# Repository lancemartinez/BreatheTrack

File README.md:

# BreatheTrack

## Prototype 1

## Assembled Prototype 1 

## Prototype 2

## Bill of Materials (BOM)

| Component                           | Quantity | Price Estimate | Link |
|-------------------------------------|----------|----------------|------|
| PCB                                 | 1        | $60            | [JLCPCB](https://jlcpcb.com) |
| 6V 1W Solar Cell                     | 5        | $16            | [Amazon](https://www.amazon.com/gp/product/B0BML3PR4Z/ref=ox_sc_act_title_1?smid=A2MJCDED57HY1D&th=1) |
| MakerFocus ESP32 LoRa V3 Dev Board (with 2x SX1262 + 2x Battery) | 1 | $53 | [Amazon](https://www.amazon.com/gp/product/B0DMSGL2DC/ref=ox_sc_act_title_1?smid=A1N6DLY3NQK2VM&th=1) |
| Solar Panel Power Manager           | 1        | $14            | [Amazon](https://www.amazon.com/gp/product/B07MML4YJV/ref=ox_sc_act_title_4?smid=A2EH5PO307BR7O&psc=1) |
| Breadboard, Resistors, LEDs Kit     | 1        | $10            | [Amazon](https://www.amazon.com/dp/B01ERP6WL4) |
| Soldering Iron                      | 1        | $9             | [Amazon](https://www.amazon.com/Soldering-Welding-Portable-Electric-Repairing/dp/B098JD8HD3) |
| Total                        | 10          | $162             | N/A |

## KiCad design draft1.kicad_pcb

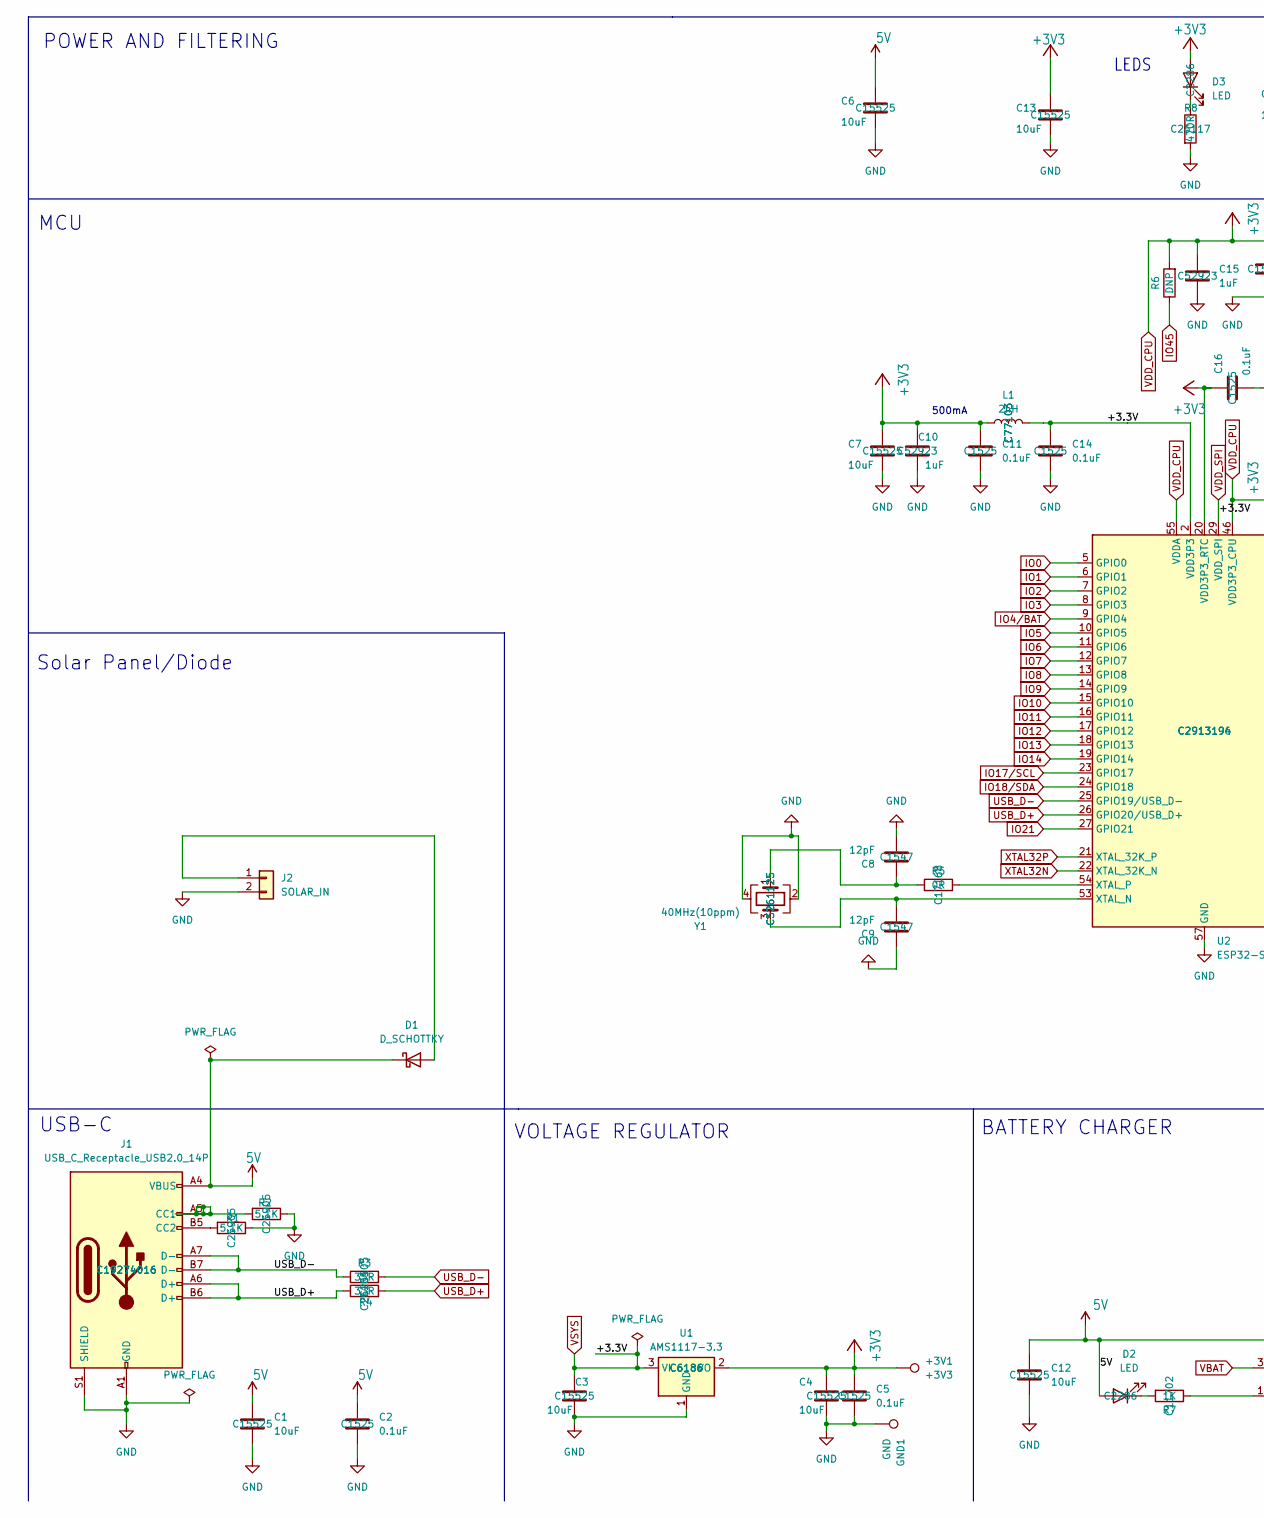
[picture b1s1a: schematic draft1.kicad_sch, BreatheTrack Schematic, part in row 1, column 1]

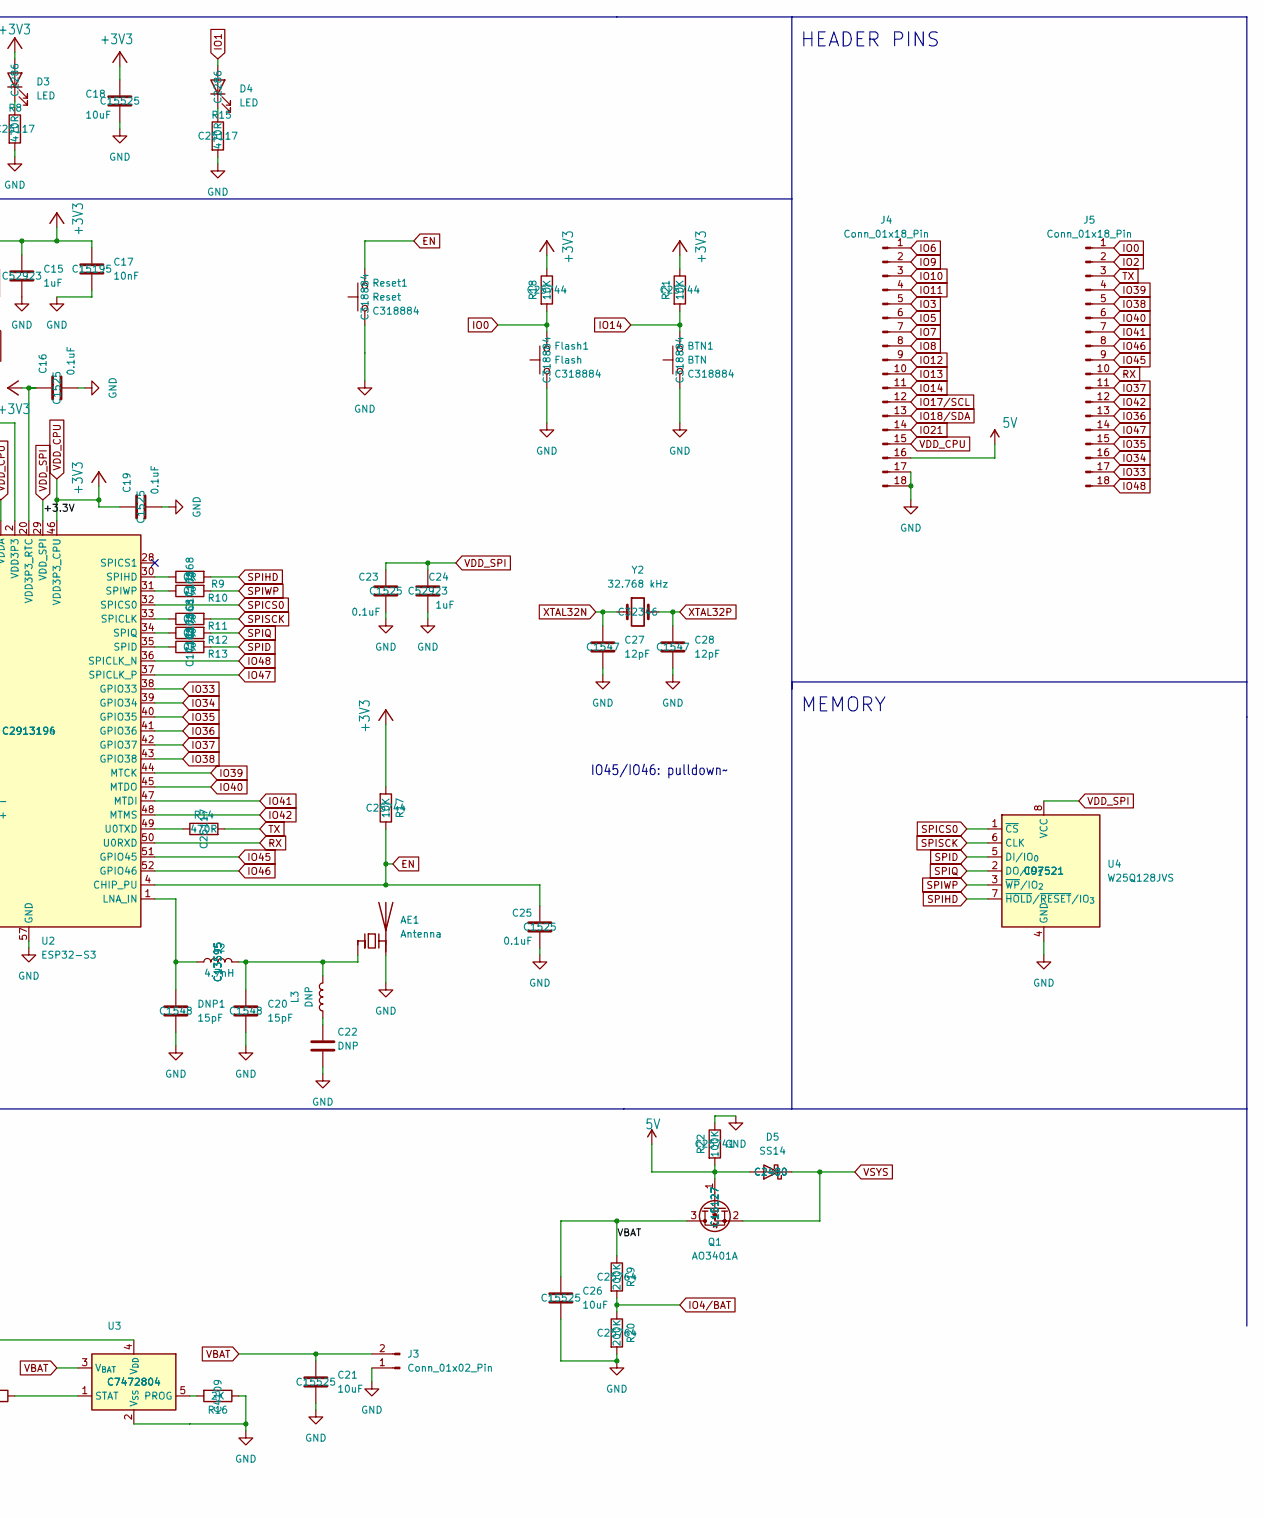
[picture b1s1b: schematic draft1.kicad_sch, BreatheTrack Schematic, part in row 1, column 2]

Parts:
+3V1: +3V3; TestPoint_Pad_D1.0mm
AE1: Antenna; Texas_SWRA117D_2.4GHz_Left
BTN1: BTN; SW_Push_1P1T_XKB_TS-1187A; MNF PART NUMBER C318884; LCSC C318884
C1, C3, C4, C6, C7, C12, C13, C18, C21, C26: 10uF; C_0402_1005Metric; MNF PART NUMBER C15525; LCSC C15525
C2, C5, C11, C14, C16, C19, C23, C25: 0.1uF; C_0402_1005Metric; MNF PART NUMBER C1525; LCSC C1525
C8, C9, C27, C28: 12pF; C_0402_1005Metric; MNF PART NUMBER C1547; LCSC C1547
C10, C15, C24: 1uF; C_0402_1005Metric; MNF PART NUMBER C52923; LCSC C52923
C17: 10nF; C_0402_1005Metric; MNF PART NUMBER C15195; LCSC C15195
C20: 15pF; C_0402_1005Metric; MNF PART NUMBER C1548; LCSC C1548
C22: DNP; C_0402_1005Metric
D1: D_SCHOTTKY; D_SMA
D2, D3, D4: LED; LED_0603_1608Metric; MNF PART NUMBER C2286; LCSC C2286
D5: SS14; D_SMA; MNF PART NUMBER C2480; LCSC C2480
DNP1: 15pF; C_0402_1005Metric; MNF PART NUMBER C1548; LCSC C1548
Flash1: Flash; SW_Push_1P1T_XKB_TS-1187A; MNF PART NUMBER C318884; LCSC C318884
GND1: GND; TestPoint_Pad_D1.0mm
J1: USB_C_Receptacle_USB2.0_14P; USB_C_Receptacle_HCTL_HC-TYPE-C-16P-01A; MNF PART NUMBER C19274016; LCSC C19274016
J2: SOLAR_IN; JST_PH_S2B-PH-SM4-TB_1x02-1MP_P2.00mm_Horizontal
J3: Conn_01x02_Pin; PinSocket_1x02_P2.54mm_Vertical
J4, J5: Conn_01x18_Pin; PinHeader_1x18_P2.54mm_Vertical
L1: 2nH; L_0402_1005Metric; MNF PART NUMBER C77103; LCSC C77103
L2: 4.7nH; L_0402_1005Metric; MNF PART NUMBER C13595; LCSC C13595
L3: DNP; L_0402_1005Metric
Q1: AO3401A; SOT-23; MNF PART NUMBER C15127; LCSC C15127
R1, R2: 5.1K; R_0402_1005Metric; MNF PART NUMBER C25905; LCSC C25905
R3, R4: 33R; R_0402_1005Metric; MNF PART NUMBER C25105; LCSC C25105
R5, R9, R10, R11, R12, R13: 0R; R_0402_1005Metric; MNF PART NUMBER C17168; LCSC C17168
R6: DNP; R_0402_1005Metric
R7: 1K; R_0402_1005Metric; MNF PART NUMBER C11702; LCSC C11702
R8, R14, R15: 470R; R_0402_1005Metric; MNF PART NUMBER C25117; LCSC C25117
R16: 2K; R_0402_1005Metric; MNF PART NUMBER C4109; LCSC C4109
R17, R18, R21: 10K; R_0402_1005Metric; MNF PART NUMBER C25744; LCSC C25744
R19, R20: 200K; R_0402_1005Metric; MNF PART NUMBER C25764; LCSC C25764
R22: 100K; R_0402_1005Metric; MNF PART NUMBER C25741; LCSC C25741
Reset1: Reset; SW_Push_1P1T_XKB_TS-1187A; MNF PART NUMBER C318884; LCSC C318884
U1: AMS1117-3.3; SOT-223-3_TabPin2; MNF PART NUMBER C6186; LCSC C6186
U2: ESP32-S3; QFN-56-1EP_7x7mm_P0.4mm_EP4x4mm; MNF PART NUMBER C2913196; LCSC C2913194
U3: MCP73831-2-OT; SOT-23-5; MNF PART NUMBER C7472804; LCSC C7472804
U4: W25Q128JVS; SOIC-8_5.3x5.3mm_P1.27mm; MNF PART NUMBER C97521; LCSC C97521
Y1: 40MHz(10ppm); Crystal_SMD_2520-4Pin_2.5x2.0mm; MNF PART NUMBER C5261125; LCSC C5261125
Y2: 32.768 kHz; Crystal_SMD_3215-2Pin_3.2x1.5mm; MNF PART NUMBER C32346; LCSC C32346

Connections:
5V: C1.1, C2.1, C6.1, C12.1, D1.1 (K), D2.2 (A), D5.2 (A), J1.A4 (VBUS), J1.A9 (VBUS), J1.B4 (VBUS), J1.B9 (VBUS), J4.16, Q1.1 (G), R22.2, U3.4 (V_{DD})
EN: C25.1, R17.1, Reset1.2, U2.4 (CHIP_PU)
GND: AE1.2 (PCB_Trace), BTN1.1, C1.2, C2.2, C3.2, C4.2, C5.2, C6.2, C7.2, C8.2, C9.1, C10.2, C11.2, C12.2, C13.2, C14.2, C15.2, C16.2, C17.2, C18.2, C19.2, C20.2, C21.2, C22.2, C23.2, C24.2, C25.2, C26.2, C27.2, C28.2, DNP1.2, Flash1.1, GND1.1, J1.A1 (GND), J1.A12 (GND), J1.B1 (GND), J1.B12 (GND), J1.S1 (SHIELD), J2.2, J3.1, J4.17, J4.18, R1.1, R2.1, R8.2, R15.2, R16.1, R20.2, R22.1, Reset1.1, U1.1 (GND), U2.57 (GND), U3.2 (V_{SS}), U4.4 (GND), Y1.2, Y1.4
IO0: Flash1.2, J5.1, R18.2, U2.5 (GPIO0)
IO1: D4.2 (A), U2.6 (GPIO1)
IO2: J5.2, U2.7 (GPIO2)
IO3: J4.5, U2.8 (GPIO3)
IO4/BAT: R19.2, R20.1, U2.9 (GPIO4)
IO5: J4.6, U2.10 (GPIO5)
IO6: J4.1, U2.11 (GPIO6)
IO7: J4.7, U2.12 (GPIO7)
IO8: J4.8, U2.13 (GPIO8)
IO9: J4.2, U2.14 (GPIO9)
IO10: J4.3, U2.15 (GPIO10)
IO11: J4.4, U2.16 (GPIO11)
IO12: J4.9, U2.17 (GPIO12)
IO13: J4.10, U2.18 (GPIO13)
IO14: BTN1.2, J4.11, R21.2, U2.19 (GPIO14)
IO17/SCL: J4.12, U2.23 (GPIO17)
IO18/SDA: J4.13, U2.24 (GPIO18)
IO21: J4.14, U2.27 (GPIO21)
IO33: J5.17, U2.38 (GPIO33)
IO34: J5.16, U2.39 (GPIO34)
IO35: J5.15, U2.40 (GPIO35)
IO36: J5.13, U2.41 (GPIO36)
IO37: J5.11, U2.42 (GPIO37)
IO38: J5.5, U2.43 (GPIO38)
IO39: J5.4, U2.44 (MTCK)
IO40: J5.6, U2.45 (MTDO)
IO41: J5.7, U2.47 (MTDI)
IO42: J5.12, U2.48 (MTMS)
IO45: J5.9, R6.1, U2.51 (GPIO45)
IO46: J5.8, U2.52 (GPIO46)
IO47: J5.14, U2.37 (SPICLK_P)
IO48: J5.18, U2.36 (SPICLK_N)
unnamed: AE1.1 (FEED), C20.1, L2.2, L3.2
unnamed: C8.1, R5.1, Y1.1
unnamed: C22.1, L3.1
unnamed: D1.2 (A), J2.1
unnamed: D2.1 (K), R7.2
unnamed: D3.1 (K), R8.1
unnamed: D4.1 (K), R15.1
unnamed: J1.A5 (CC1), R2.2
unnamed: J1.B5 (CC2), R1.2
unnamed: DNP1.1, L2.1, U2.1 (LNA_IN)
unnamed: R11.1, U2.33 (SPICLK)
unnamed: R13.1, U2.35 (SPID)
unnamed: R9.1, U2.30 (SPIHD)
unnamed: R12.1, U2.34 (SPIQ)
unnamed: R10.1, U2.31 (SPIWP)
unnamed: R14.1, U2.49 (U0TXD)
unnamed: C9.2, U2.53 (XTAL_N), Y1.3
unnamed: R5.2, U2.54 (XTAL_P)
unnamed: R16.2, U3.5 (PROG)
unnamed: R7.1, U3.1 (STAT)
RX: J5.10, U2.50 (U0RXD)
SPICS0: U2.32 (SPICS0), U4.1 (~CS)
SPID: R13.2, U4.5 (DI/IO_{0})
SPIHD: R9.2, U4.7 (~HOLD/~RESET/IO_{3})
SPIQ: R12.2, U4.2 (DO/IO_{1})
SPISCK: R11.2, U4.6 (CLK)
SPIWP: R10.2, U4.3 (~WP/IO_{2})
TX: J5.3, R14.2
USB_D+: J1.A6 (D+), J1.B6 (D+), R4.1, R4.2, U2.26 (GPIO20/USB_D+)
USB_D-: J1.A7 (D-), J1.B7 (D-), R3.1, R3.2, U2.25 (GPIO19/USB_D-)
VBAT: C21.1, C26.1, J3.2, Q1.3 (D), R19.1, U3.3 (V_{BAT})
VDD_CPU: +3V1.1, C4.1, C5.1, C7.1, C10.1, C11.1, C13.1, C15.1, C16.1, C17.1, C18.1, C19.1, D3.2 (A), J4.15, L1.1, R6.2, R17.2, R18.1, R21.1, U1.2 (VO), U2.20 (VDD3P3_RTC), U2.46 (VDD3P3_CPU), U2.55 (VDDA), U2.56 (VDDA)
VDD_SPI: C3.1, C14.1, C23.1, C24.1, D5.1 (K), L1.2, Q1.2 (S), U1.3 (VI), U2.2 (VDD3P3), U2.3 (VDD3P3), U2.29 (VDD_SPI), U4.8 (VCC)
XTAL32N: C27.1, U2.22 (XTAL_32K_N), Y2.1
XTAL32P: C28.1, U2.21 (XTAL_32K_P), Y2.2

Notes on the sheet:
Solar Panel/Diode
500mA
MCU
USB-C
BATTERY CHARGER
MEMORY
VOLTAGE REGULATOR
IO45/IO46: pulldown~~{}
POWER AND FILTERING
HEADER PINS
LEDS

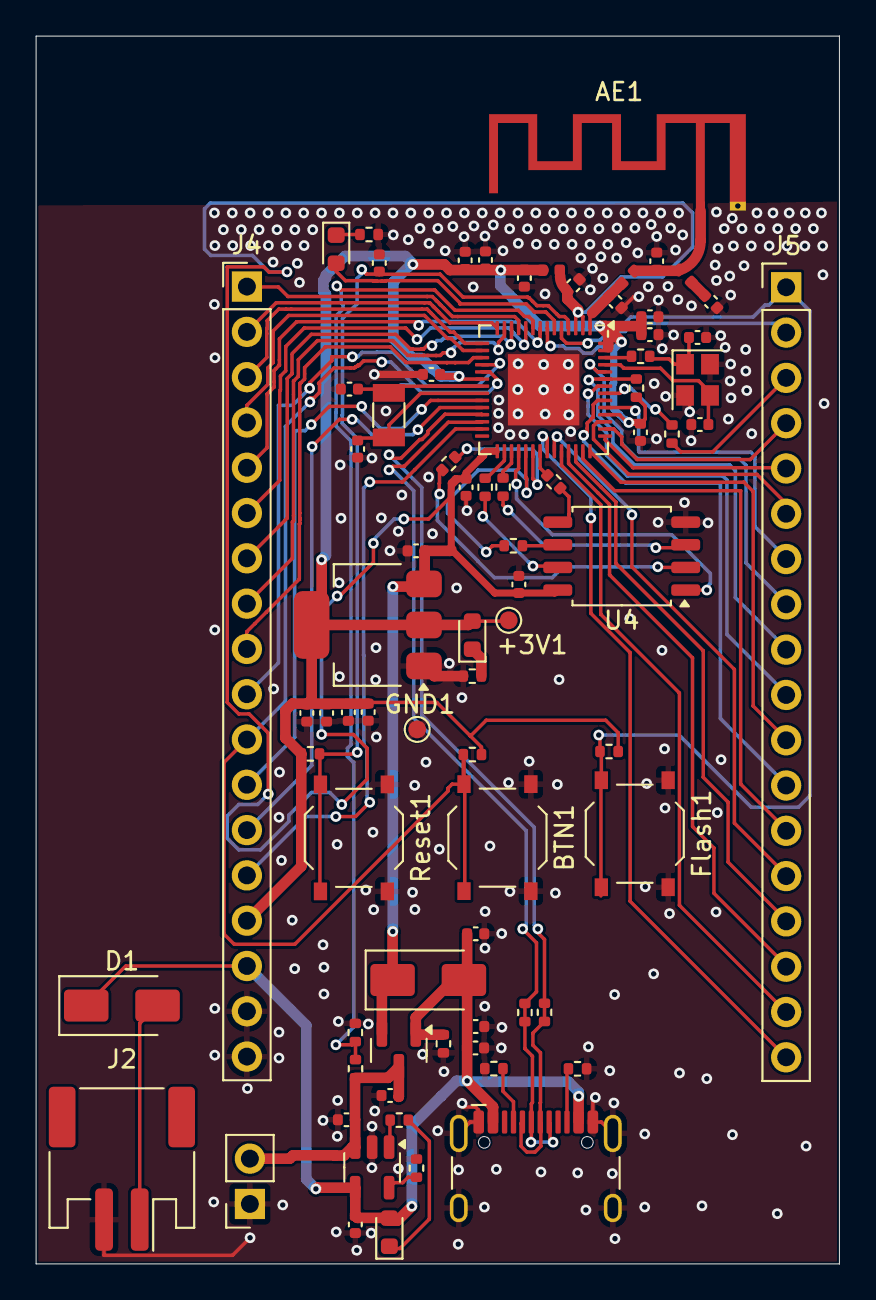
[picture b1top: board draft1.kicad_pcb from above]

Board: 4 copper layers, 45.1 x 68.8 mm, 77 parts (0 on the bottom side), 70 nets.

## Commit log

2025-06-20 Create JOURNAL
2025-06-27 Added images
2025-06-27 Circuit Diagram Added
2025-06-27 Added Sschematic
2025-06-27 Board
2025-06-27 Added Gerber Files
2025-06-27 Organization
2025-06-27 Added gerber
2025-06-30 Added CAD
2025-07-01 Added Flask
2025-07-01 Added scripts
2025-07-02 Added .step
2025-07-22 Heltec Code
2025-07-23 Meshtastic Firmware
2025-07-23 gitignore
2025-07-23 receiver
2025-07-24 Added HTTP
2025-07-29 Logo
2025-07-31 Images
2025-07-31 edit
